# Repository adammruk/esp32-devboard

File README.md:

# ESP32 Development Board

## Why a new development board?

Currently, there are many different development boards for ESP32 available on the market. I have also been using various different ones - ESP32-Cam, ESP32 WROOM, ESP32 WROOM on a board with buttons, MicroUSB port, and GPIO ports, ESP32 module with an LCD display, etc. Every board has some nice features, but overall I have always been missing the things that I believe a dev board should have:

- easy access to GPIO; most of the boards have a really inconvenient access to GPIO pins, making it harder to connect/disconnect cables
- properly described microcontroller pins, especially GPIO. This is the thing that widely used boards do the worst. Instead of using real pin descriptions, most of them use Arduino-based numbers (like 1, 2, 3 instead of GPIO01, GPIO02, etc). It may not be a big deal while using Arduino, but it's really problematic when using ESP-IDF
- easy to connect a logic analyzer or oscilloscope to GPIO. If not using a breadboard, it's complicated to connect two cables to one GPIO
- dedicated port for JTAG and serial port
- a few buttons and LEDs for generic purposes
- LOTS of power and GND pins

This made me think to create a new development board to address all of those issues.

## Features

1. Easy access to GPIO boards with clear descriptions
2. Designed to work with popular Saleae logic analyzer but compatible with all logic analyzers or oscilloscopes
3. Compatible with [ESP-Prog](https://docs.espressif.com/projects/espressif-esp-iot-solution/en/latest/hw-reference/ESP-Prog_guide.html) JTAG and UART
4. General purpose buttons and LEDs
5. Easily accessible power pins (5V, 3.3V and GND) on both sides of the board

## Opening project
Just open projects files in KiCad. Every symbol and footpring should be automatically imported.

## Contributing

Just create a Pull Request with your changes, make sure to describe and explain the changes you would like to make. If you'll encounter any errors, [feel free to create an issue.](https://github.com/adammruk/esp32-devboard/issues)

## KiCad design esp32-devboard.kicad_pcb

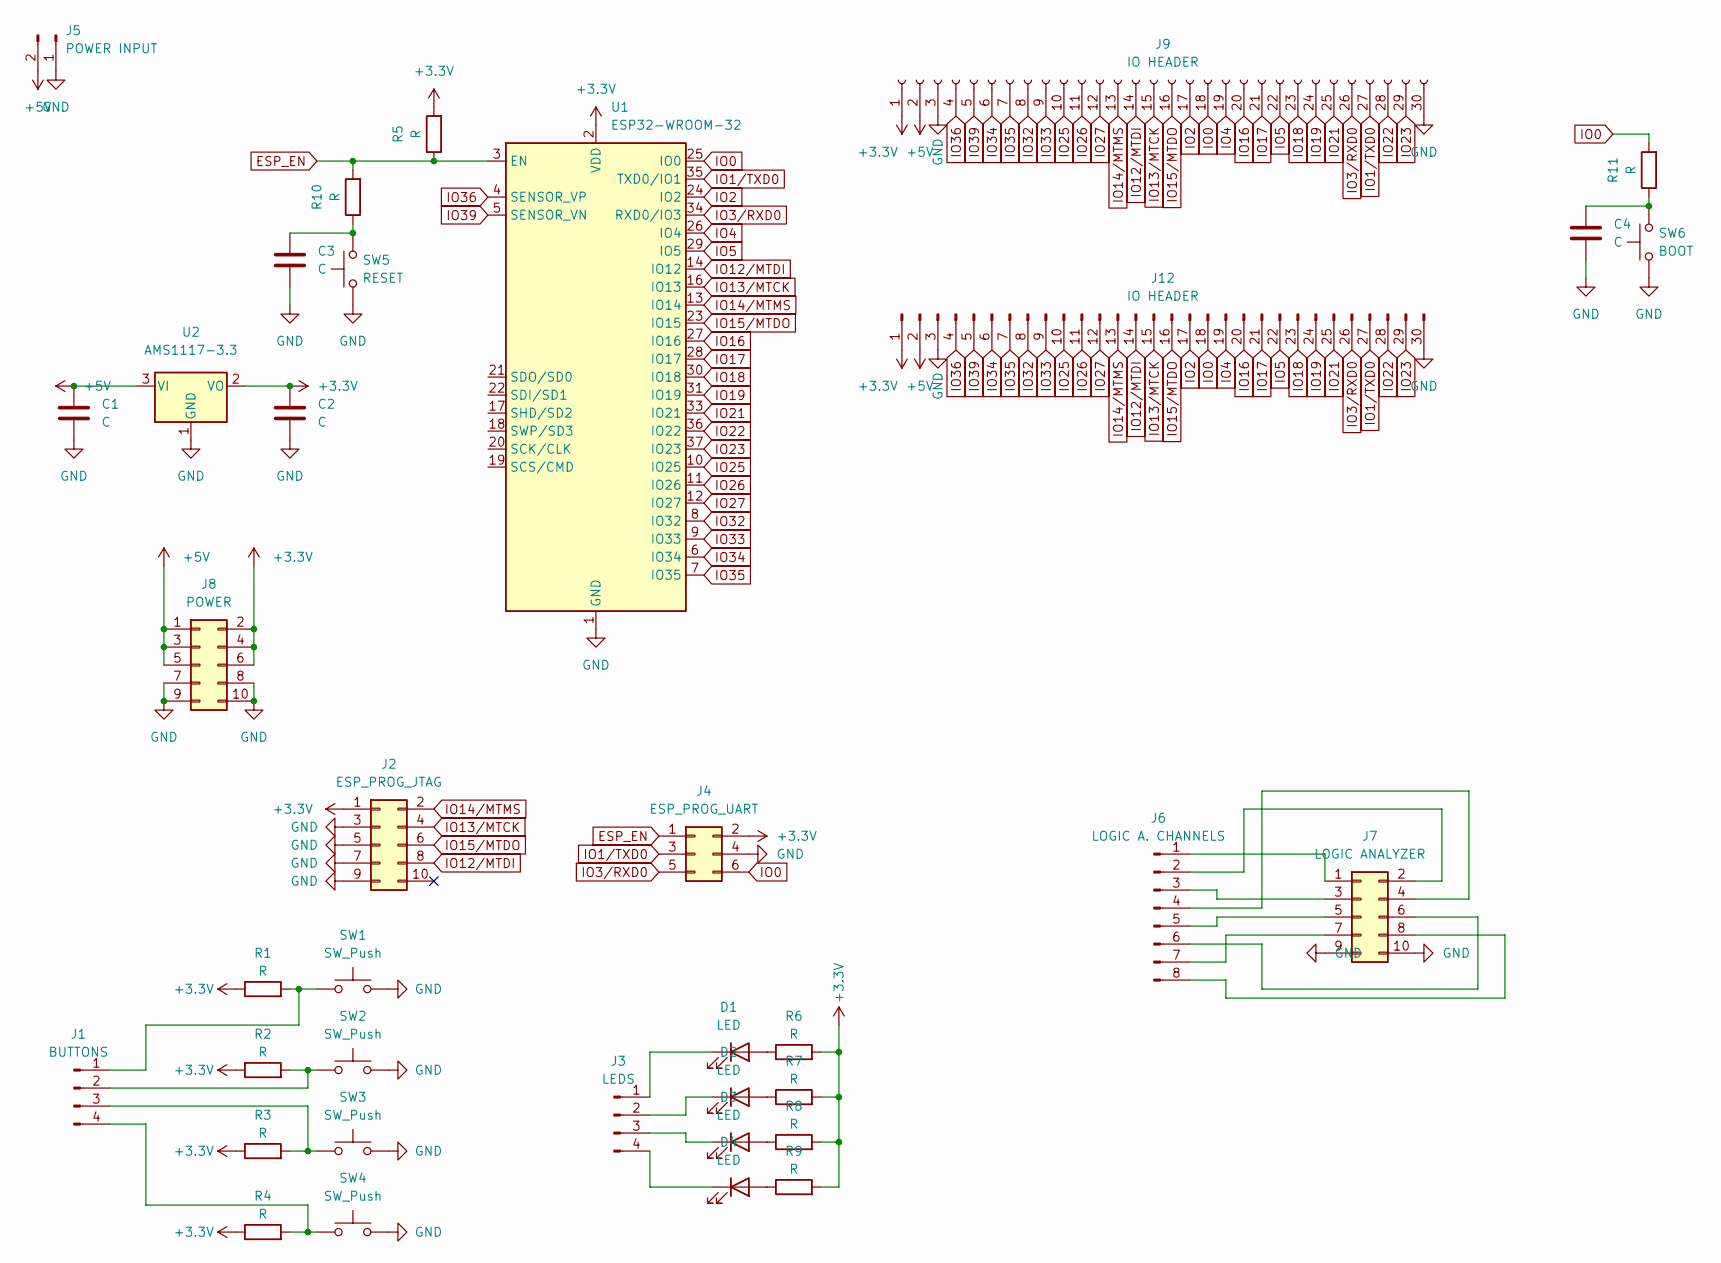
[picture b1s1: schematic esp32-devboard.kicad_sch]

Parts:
C1, C2, C3, C4: C; C_1206_3216Metric
D1, D2, D3, D4: LED; LED_1210_3225Metric
J1: BUTTONS; PinHeader_1x04_P2.54mm_Vertical
J2: ESP_PROG_JTAG; IDC-Header_2x05_P2.54mm_Vertical
J3: LEDS; PinHeader_1x04_P2.54mm_Vertical
J4: ESP_PROG_UART; IDC-Header_2x03_P2.54mm_Vertical
J5: POWER INPUT; PinHeader_1x02_P2.54mm_Vertical
J6: LOGIC A. CHANNELS; PinHeader_1x08_P2.54mm_Vertical
J7: LOGIC ANALYZER; IDC-Header_2x05_P2.54mm_Vertical
J8: POWER; PinHeader_2x05_P2.54mm_Vertical
J9: IO HEADER; PinSocket_1x30_P2.54mm_Horizontal
J12: IO HEADER; PinHeader_1x30_P2.54mm_Vertical
R1, R2, R3, R4, R5, R6, R7, R8, R9, R10, R11: R; R_1206_3216Metric
SW1, SW2, SW3, SW4: SW_Push; SW_SPST_TL3342
SW5: RESET; SW_SPST_TL3342
SW6: BOOT; SW_SPST_TL3342
U1: ESP32-WROOM-32
U2: AMS1117-3.3; SOT-223-3_TabPin2

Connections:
+3V3: C2.2, J2.1, J4.2, J8.2, J8.4, J8.6, J9.1, J12.1, R1.1, R2.1, R3.1, R4.1, R5.2, R6.2, R7.2, R8.2, R9.2, U1.2 (VDD), U2.2 (VO)
+5V: C1.2, J5.2, J8.1, J8.3, J8.5, J9.2, J12.2, U2.3 (VI)
ESP_EN: J4.1, R5.1, R10.2, U1.3 (EN)
GND: C1.1, C2.1, C3.1, C4.1, J2.3, J2.5, J2.7, J2.9, J4.4, J5.1, J7.9, J7.10, J8.7, J8.8, J8.9, J8.10, J9.3, J9.30, J12.3, J12.30, SW1.2, SW2.2, SW3.2, SW4.2, SW5.1, SW6.1, U1.1 (GND), U1.15 (GND), U1.38 (GND), U1.39 (GND), U2.1 (GND)
IO0: J4.6, J9.18, J12.18, R11.2, U1.25 (IO0)
IO1/TXD0: J4.3, J9.27, J12.27, U1.35 (TXD0/IO1)
IO2: J9.17, J12.17, U1.24 (IO2)
IO3/RXD0: J4.5, J9.26, J12.26, U1.34 (RXD0/IO3)
IO4: J9.19, J12.19, U1.26 (IO4)
IO5: J9.22, J12.22, U1.29 (IO5)
IO12/MTDI: J2.8, J9.14, J12.14, U1.14 (IO12)
IO13/MTCK: J2.4, J9.15, J12.15, U1.16 (IO13)
IO14/MTMS: J2.2, J9.13, J12.13, U1.13 (IO14)
IO15/MTDO: J2.6, J9.16, J12.16, U1.23 (IO15)
IO16: J9.20, J12.20, U1.27 (IO16)
IO17: J9.21, J12.21, U1.28 (IO17)
IO18: J9.23, J12.23, U1.30 (IO18)
IO19: J9.24, J12.24, U1.31 (IO19)
IO21: J9.25, J12.25, U1.33 (IO21)
IO22: J9.28, J12.28, U1.36 (IO22)
IO23: J9.29, J12.29, U1.37 (IO23)
IO25: J9.10, J12.10, U1.10 (IO25)
IO26: J9.11, J12.11, U1.11 (IO26)
IO27: J9.12, J12.12, U1.12 (IO27)
IO32: J9.8, J12.8, U1.8 (IO32)
IO33: J9.9, J12.9, U1.9 (IO33)
IO34: J9.6, J12.6, U1.6 (IO34)
IO35: J9.7, J12.7, U1.7 (IO35)
IO36: J9.4, J12.4, U1.4 (SENSOR_VP)
IO39: J9.5, J12.5, U1.5 (SENSOR_VN)
unnamed: C3.2, R10.1, SW5.2
unnamed: C4.2, R11.1, SW6.2
unnamed: D1.2 (A), R6.1
unnamed: D1.1 (K), J3.1
unnamed: D2.2 (A), R7.1
unnamed: D2.1 (K), J3.2
unnamed: D3.2 (A), R8.1
unnamed: D3.1 (K), J3.3
unnamed: D4.2 (A), R9.1
unnamed: D4.1 (K), J3.4
unnamed: J1.1, R1.2, SW1.1
unnamed: J1.2, R2.2, SW2.1
unnamed: J1.3, R3.2, SW3.1
unnamed: J1.4, R4.2, SW4.1
unnamed: J6.1, J7.1
unnamed: J6.2, J7.2
unnamed: J6.3, J7.3
unnamed: J6.4, J7.4
unnamed: J6.5, J7.5
unnamed: J6.6, J7.6
unnamed: J6.7, J7.7
unnamed: J6.8, J7.8

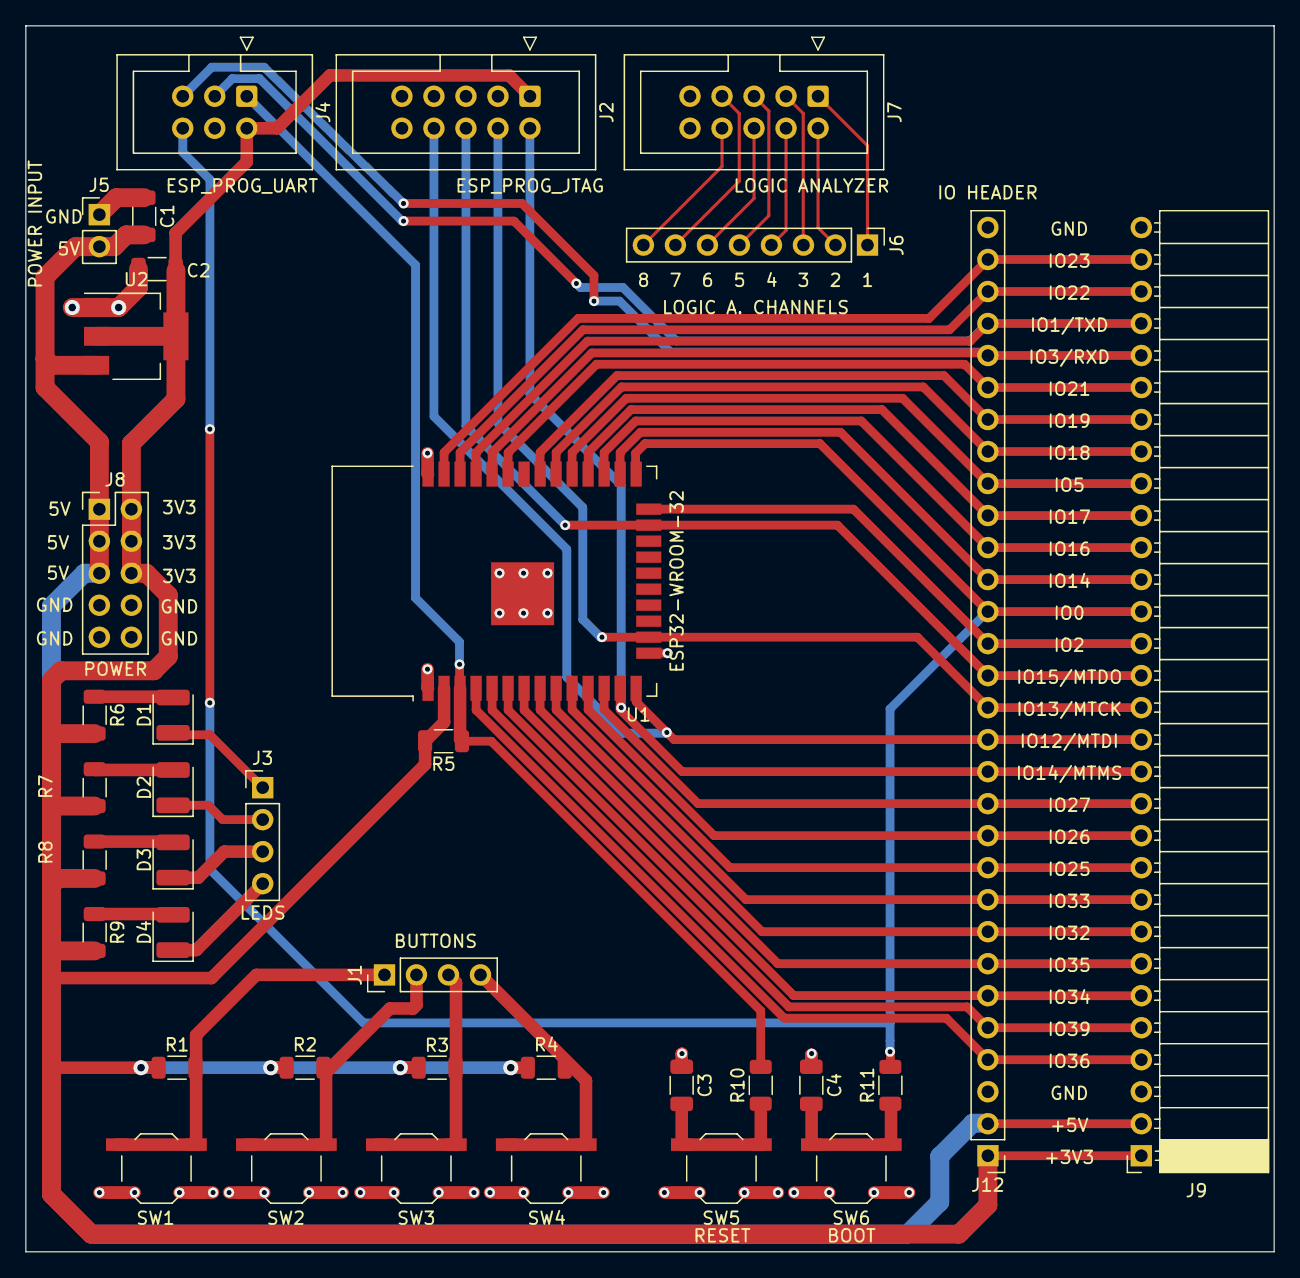
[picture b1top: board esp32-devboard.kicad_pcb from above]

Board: 2 copper layers, 99.1 x 97.3 mm, 37 parts (0 on the bottom side), 52 nets.

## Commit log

2024-04-16 init commit
2024-04-16 Create LICENSE
